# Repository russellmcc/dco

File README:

This is a nascent, unfinished design for an incredibly cost-sensitive DCO module for eurorack format modular synthesizers.

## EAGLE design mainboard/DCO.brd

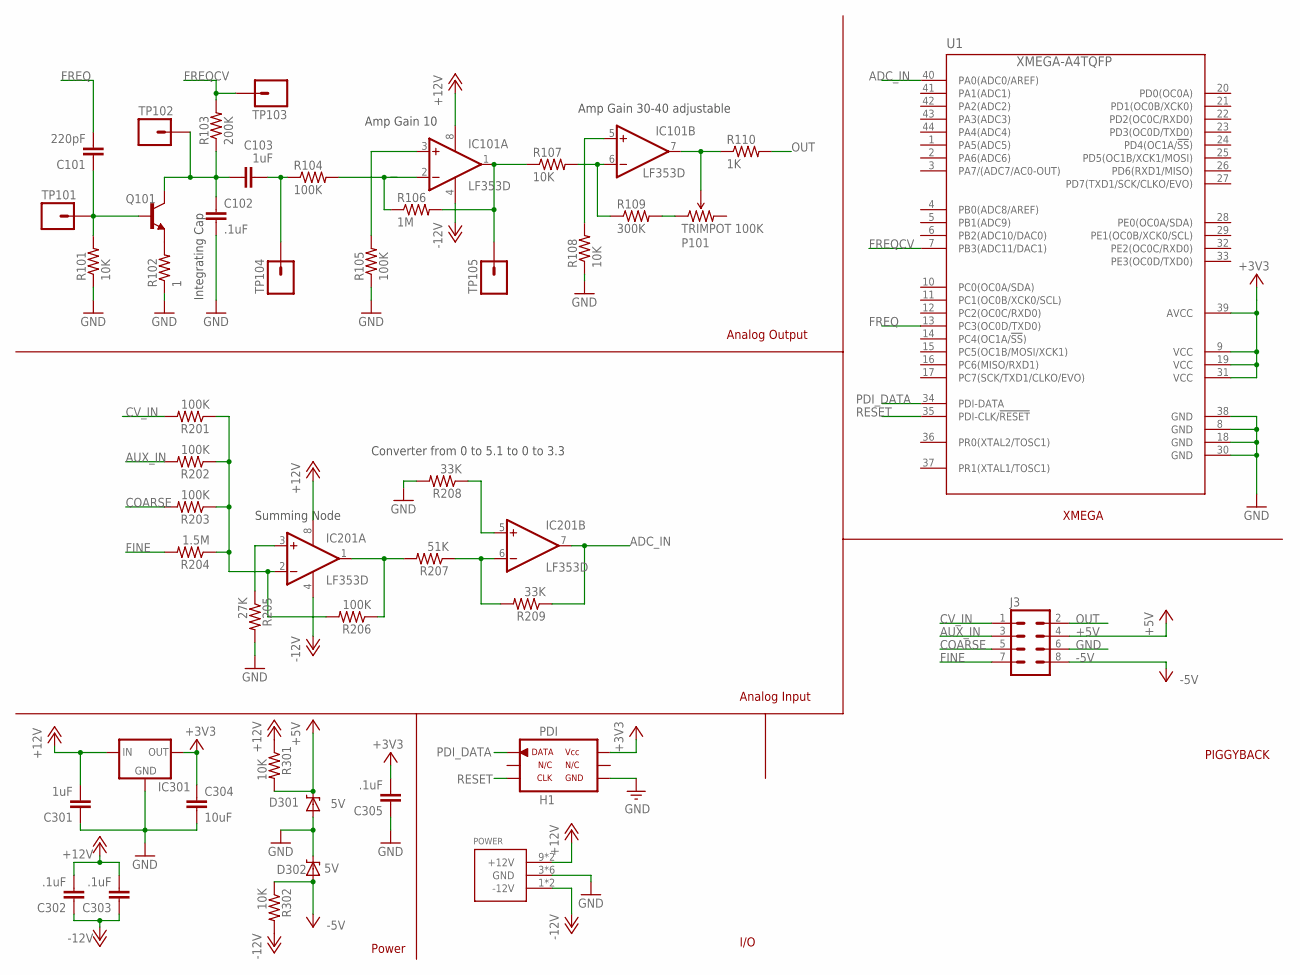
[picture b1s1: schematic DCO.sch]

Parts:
C101: 220pF; 0603-CAP
C102: .1uF; 1210
C103, C301: 1uF; 0805
C302, C303, C305: .1uF; 0603-CAP
C304: 10uF; 1206
D301, D302: 5V; SOD-323
H1: PDI; AVR_ISP_6
IC101, IC201: LF353D; SO08
IC301: V_REG_MIC2920; SOT223
J3: M04X2; 2X4
P101: TRIMPOT 100K; TRIM_POT_PTH
POWER: POWER_SIMPLE16; POWER_16
Q101: TRANSISTOR_NPNSOT23; SOT23
R101, R107, R108, R301, R302: 10K; 0603-RES
R102: 1; 0805
R103: 200K; 0603-RES
R104, R105, R201, R202, R203, R206: 100K; 0603-RES
R106: 1M; 0603-RES
R109: 300K; 0603-RES
R110: 1K; 0603-RES
R204: 1.5M; 0603-RES
R205: 27K; 0603-RES
R207: 51K; 0603-RES
R208, R209: 33K; 0603-RES
TP101, TP102, TP103, TP104, TP105: M01PTH; 1X01
U1: XMEGA-A4TQFP; TQFP44

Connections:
+3V3: C304.1, C305.2, H1.P$2 (VCC_IO), IC301.3 (OUT), U1.9 (VCC), U1.19 (VCC), U1.31 (VCC), U1.39 (AVCC)
+5V: D301.1 (C), J3.4, R301.2
+12V: C301.2, C302.2, C303.2, IC101.8 (V+), IC201.8 (V+), IC301.1 (IN), POWER.9 (+12V), POWER.10 (+12V), R301.1
-5V: D302.2 (A), J3.8, R302.1
-12V: C302.1, C303.1, IC101.4 (V-), IC201.4 (V-), POWER.1 (-12V), POWER.2 (-12V), R302.2
ADC_IN: IC201.7 (OUT), R209.1, U1.40 (PA0(ADC0/AREF))
AUX_IN: J3.3, R202.2
COARSE: J3.5, R203.2
CV_IN: J3.1, R201.2
FINE: J3.7, R204.2
FREQ: C101.2, U1.13 (PC3(OC0D/TXD0))
FREQCV: R103.2, TP103.1, U1.7 (PB3(ADC11/DAC1))
GND: C102.2, C301.1, C304.2, C305.1, D301.2 (A), D302.1 (C), H1.P$6 (GND), IC301.2 (GND), J3.6, POWER.3 (GND), POWER.4 (GND), POWER.5 (GND), POWER.6 (GND), POWER.7 (GND), POWER.8 (GND), R101.1, R102.1, R105.1, R108.1, R205.2, R208.2, U1.8 (GND), U1.18 (GND), U1.30 (GND), U1.38 (GND)
unnamed: C102.1, C103.1, Q101.3 (C), R103.1, TP102.1
unnamed: C101.1, Q101.1 (B), R101.2, TP101.1
unnamed: IC101.6 (-IN), R107.2, R109.1
unnamed: Q101.2 (E), R102.2
unnamed: C103.2, R104.1, TP104.1
unnamed: IC201.3 (+IN), R205.1
unnamed: IC101.3 (+IN), R105.2
unnamed: IC101.5 (+IN), R108.2
unnamed: IC101.7 (OUT), P101.2 (WIPER), R110.1
unnamed: P101.1 (CCW), R109.2
unnamed: IC101.1 (OUT), R106.2, R107.1, TP105.1
unnamed: IC201.1 (OUT), R206.1, R207.2
unnamed: IC201.6 (-IN), R207.1, R209.2
unnamed: IC201.5 (+IN), R208.1
OUT: J3.2, R110.2
PDI_DATA: H1.P$1 (DATA), U1.34 (PDI-DATA)
R104: IC101.2 (-IN), R104.2, R106.1
R205: IC201.2 (-IN), R201.1, R202.1, R203.1, R204.1, R206.2
RESET: H1.P$5 (CLK), U1.35 (PDI-CLK/!RESET)

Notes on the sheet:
Integrating Cap
Amp Gain 10
Amp Gain 30-40 adjustable
Summing Node
Converter from 0 to 5.1 to 0 to 3.3
Analog Output
Analog Input
Power
I/O
XMEGA
PIGGYBACK

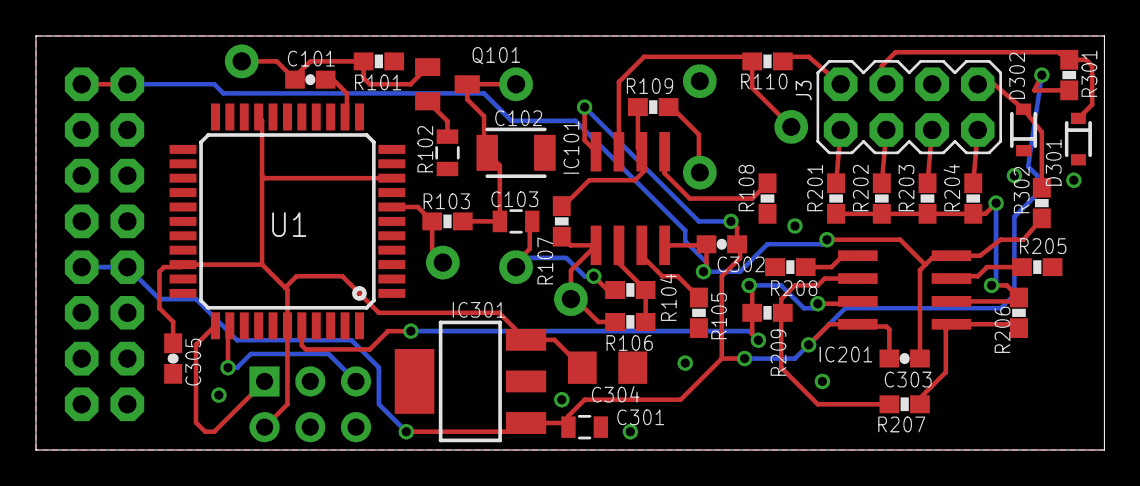
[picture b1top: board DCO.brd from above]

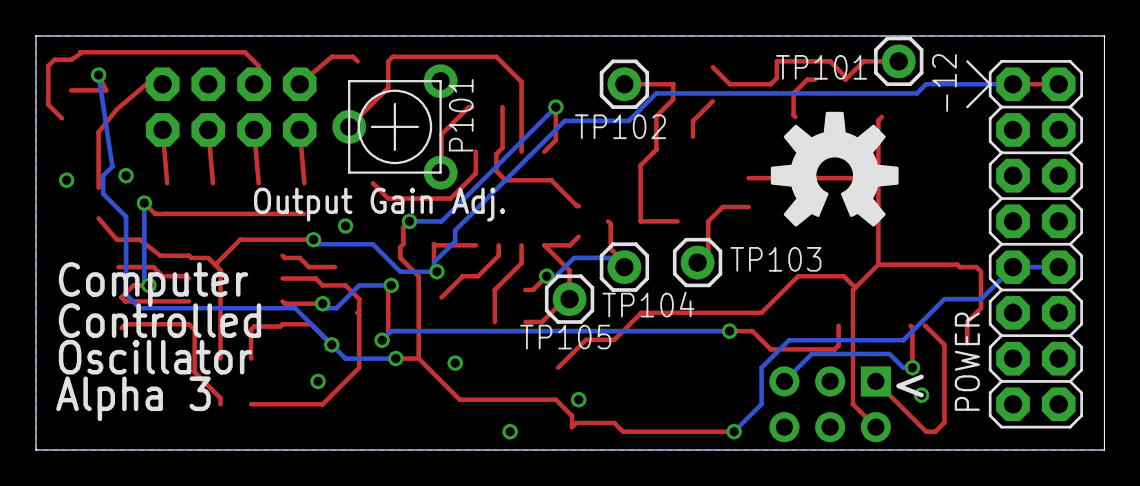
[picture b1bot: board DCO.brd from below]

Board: 2 copper layers, 59.4 x 23.0 mm, 46 parts (9 on the bottom side), 32 nets.

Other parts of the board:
U$1: OSHW-LOGO-L

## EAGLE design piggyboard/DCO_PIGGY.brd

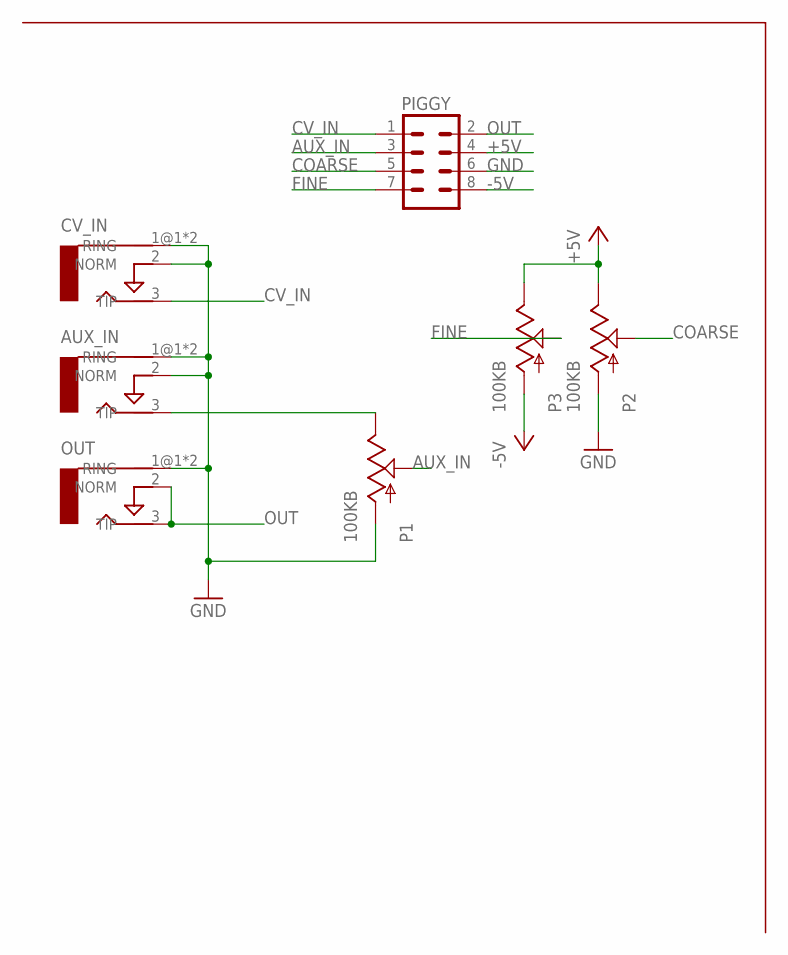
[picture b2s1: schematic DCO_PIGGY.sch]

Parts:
AUX_IN: AUDIO-JACKERTHENVAR; ERTHENVAR-JACK
CV_IN: AUDIO-JACKERTHENVAR; ERTHENVAR-JACK
OUT: AUDIO-JACKERTHENVAR; ERTHENVAR-JACK
P1, P2, P3: 100KB; PDB12
PIGGY: M04X2; 2X4

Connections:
+5V: P2.3 (E), P3.3 (E), PIGGY.4
-5V: P3.1 (A), PIGGY.8
AUX_IN: P1.2 (S), PIGGY.3
COARSE: P2.2 (S), PIGGY.5
CV_IN: CV_IN.3 (TIP), PIGGY.1
FINE: P3.2 (S), PIGGY.7
GND: AUX_IN.1@1 (RING), AUX_IN.1@2 (RING), AUX_IN.2 (NORM), CV_IN.1@1 (RING), CV_IN.1@2 (RING), CV_IN.2 (NORM), OUT.1@1 (RING), OUT.1@2 (RING), P1.1 (A), P2.1 (A), PIGGY.6
unnamed: AUX_IN.3 (TIP), P1.3 (E)
OUT: OUT.2 (NORM), OUT.3 (TIP), PIGGY.2

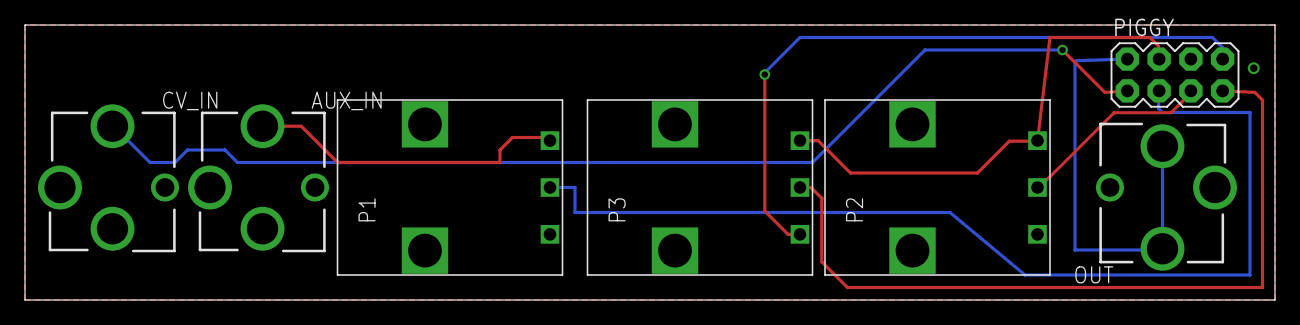
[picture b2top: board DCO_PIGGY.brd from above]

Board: 2 copper layers, 100.0 x 22.0 mm, 7 parts (0 on the bottom side), 9 nets.

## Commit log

2012-12-24 initial
2012-12-26 Changed isolation settings on ground planes for piggy back board
2012-12-27 added frontpanel design
2012-12-27 added license
2012-12-28 Re-laid out board, no routing
2012-12-28 added BOM
2012-12-29 updated BOM after sourcing from mouser
2012-12-29 added link to mouser order
2012-12-29 edited schematic parts after sourcing from mouser, initial board layout.
2012-12-29 brendan said it was a good idea to add a ground via near the decoupling cap for the micro
2013-01-04 Another attempt to layout DCO.
2013-01-04 Adjusted labels on top of board
2013-01-04 adjusted labels on bottom of board
2013-01-06 edited front panel
2013-01-11 fix for a messed up output jack on the piggy board
2013-01-11 added .gitignore
2013-01-17 object -> path.
2013-01-27 better hole placement
2013-02-07 fix for BOM malfunction
2013-02-07 oops!
2013-02-12 Fixed Silkscreens
2013-02-15 fix for panel
2013-02-15 fixed footprint
2013-03-01 added soldermask SVG
2013-03-01 oops - border was messed up on soldermask.
2013-06-09 rerouted, switched to TQFP xmega
2013-06-09 edited labels
2013-07-27 initial (bad) version of the firmware.
2013-07-28 Fixed design flaw - these resistors should be 10K
2013-07-28 Fix for design flaw - fine pitch control was attached backwards.
2013-08-01 basic table generator for future fast version of firmware.
2013-08-18 added table.h initial version
2013-08-28 added ability to track maximum errors in tablegen
2013-08-28 switched to using a 32-bit timer
2013-08-28 added hysteresis
2013-09-08 removed prescale hysteresis
2013-09-08 Two fixes: first, hold off on updating the prescale until after the least significant timer has updated. This should significantly reduce distortion when switching prescales. Second, don't use 0 as a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
2013-09-08 Added tuning constant to haskell generator, tuned my board.
    Added comment about how to use the digital filter in firmware.ino
    Version 1.0
2013-09-15 added info for programming

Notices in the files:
parts and their libraries:
SparkFun: Licensing: CC v3.0 Share-Alike You are welcome to use this library for commercial purposes.
